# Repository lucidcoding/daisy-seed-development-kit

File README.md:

# Daisy Seed Development Kit

## Author

Paul Davies

## Description

A modular development kit for the Electrosmith Daisy Seed development board. Currently modules include the central breakout board, a MIDI adapter and an array of 16 potentiometers. The breakout board includes connections for a second potentiometer array, SPI, I2C, an encoder and an SD card.

## Environment Setup

Ensure you have LIBDAISY_DIR and DAISYSP_DIR environment variables set and pointing to the relevant libraries. If you are using Windows, ensure they use the forward slash. If you are on Linux, ensure the capitalisation is correct. You'll make your life a lot easier if you don't have spaces in the path:

```
LIBDAISY_DIR=/path/to/libdaisy
DAISYSP_DIR=/path/to/daisysp
```

## Getting up and running

In order to build the hardware, load each of the projects in to Kicad, generate Gerber files and upload to a PCB manufacturer such as https://jlcpcb.com/. I can go into more detail about this at a later point.

The to get started, load the MonoSeed09 project on to the Daisy Seed by pressing both buttons to put it into program mode, entering the relevant folder, then enetering the commands to upload the code onto the Seed:

```
cd Examples/MonoSeed09
make clean; make; make program-dfu;
```

Ensure the Daisy Seed is correctly seated in the breakout board. Then connect the potentiometer array to port 1 with a JST XH2.54 8 wire cable, and connect the MIDI adapter with a JST XH2.54 4 wire cable. Finally connect your MIDI sequencer to the MIDI in DIN connector and plug your headphones into the audio out jack socket.

## Disclaimer

Although I am a professional programmer, I am purely a hobbyist when it comes to hardware or embedded programming. There may well be some mistakes here and I accept no responsibility for damage to you Daisy Seed, external equipment or anything else. You use this code and harware at your own risk.

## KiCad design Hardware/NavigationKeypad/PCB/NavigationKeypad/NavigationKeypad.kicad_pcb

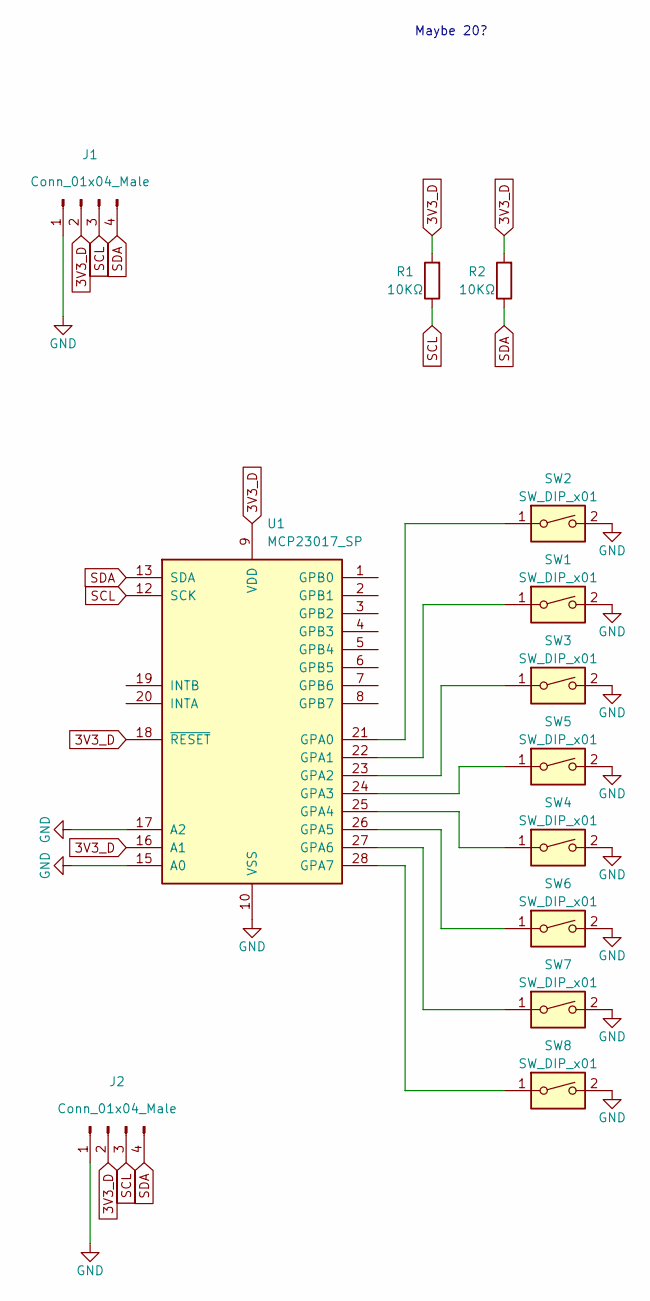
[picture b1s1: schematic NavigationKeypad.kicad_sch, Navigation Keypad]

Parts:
J1: Conn_01x04_Male; PinHeader_1x04_P2.54mm_Horizontal
J2: Conn_01x04_Male; PinSocket_1x04_P2.54mm_Horizontal
R1, R2: 10KΩ; R_Axial_DIN0207_L6.3mm_D2.5mm_P10.16mm_Horizontal
SW1, SW2, SW3, SW4, SW5, SW6, SW7, SW8: SW_DIP_x01; SW_PUSH_6mm
U1: MCP23017_SP; DIP-28_W7.62mm

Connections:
3V3_D: J1.2, J2.2, R1.2, R2.2, U1.9 (VDD), U1.16 (A1), U1.18 (~RESET)
GND: J1.1, J2.1, SW1.2, SW2.2, SW3.2, SW4.2, SW5.2, SW6.2, SW7.2, SW8.2, U1.10 (VSS), U1.15 (A0), U1.17 (A2)
unnamed: SW2.1, U1.21 (GPA0)
unnamed: SW1.1, U1.22 (GPA1)
unnamed: SW3.1, U1.23 (GPA2)
unnamed: SW5.1, U1.24 (GPA3)
unnamed: SW4.1, U1.25 (GPA4)
unnamed: SW6.1, U1.26 (GPA5)
unnamed: SW7.1, U1.27 (GPA6)
unnamed: SW8.1, U1.28 (GPA7)
SCL: J1.3, J2.3, R1.1, U1.12 (SCK)
SDA: J1.4, J2.4, R2.1, U1.13 (SDA)

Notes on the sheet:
Maybe 20?

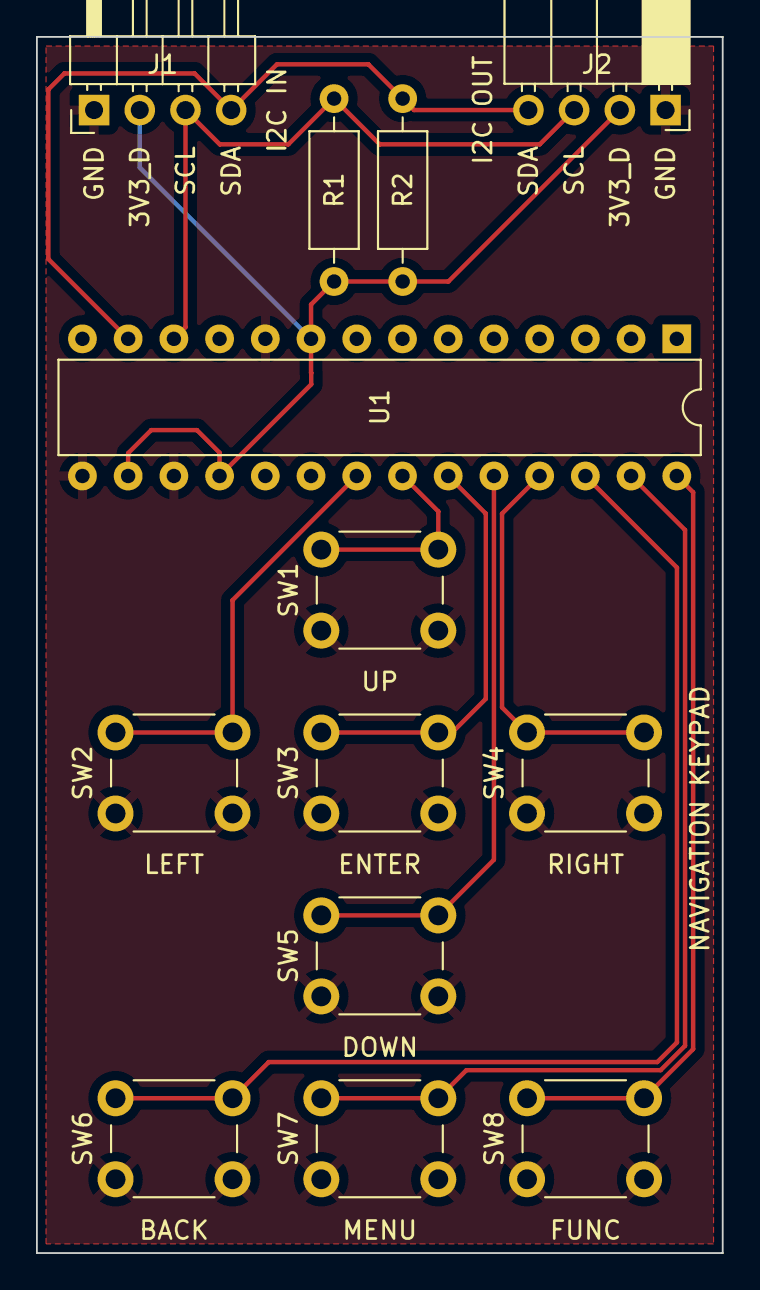
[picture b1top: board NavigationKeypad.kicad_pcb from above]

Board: 2 copper layers, 38.1 x 67.6 mm, 13 parts (0 on the bottom side), 12 nets.

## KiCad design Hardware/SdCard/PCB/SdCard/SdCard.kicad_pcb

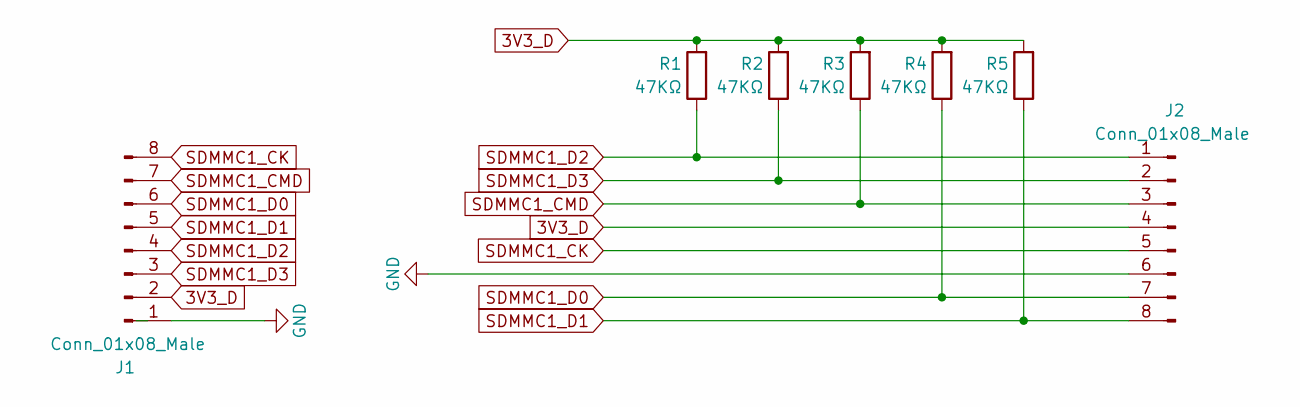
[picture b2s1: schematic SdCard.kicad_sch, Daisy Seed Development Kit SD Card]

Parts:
J1: Conn_01x08_Male; PinHeader_1x08_P2.54mm_Horizontal
J2: Conn_01x08_Male; PinHeader_1x08_P2.00mm_Vertical
R1, R2, R3, R4, R5: 47KΩ; R_Axial_DIN0207_L6.3mm_D2.5mm_P10.16mm_Horizontal

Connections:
3V3_D: J1.2, J2.4, R1.2, R2.2, R3.2, R4.2, R5.2
GND: J1.1, J2.6
SDMMC1_CK: J1.8, J2.5
SDMMC1_CMD: J1.7, J2.3, R3.1
SDMMC1_D0: J1.6, J2.7, R4.1
SDMMC1_D1: J1.5, J2.8, R5.1
SDMMC1_D2: J1.4, J2.1, R1.1
SDMMC1_D3: J1.3, J2.2, R2.1

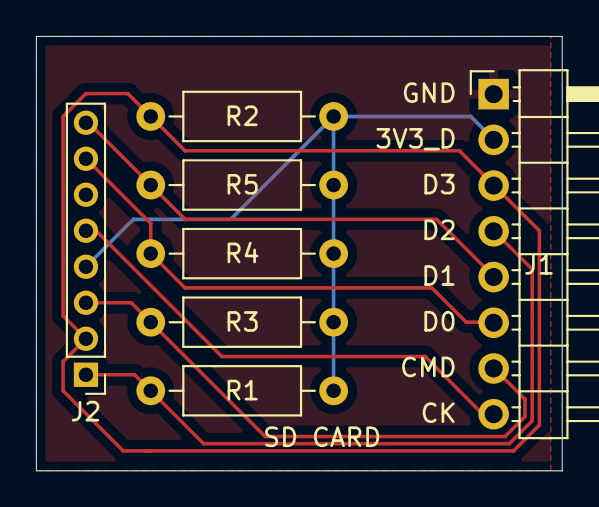
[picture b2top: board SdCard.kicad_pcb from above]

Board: 2 copper layers, 29.2 x 24.1 mm, 7 parts (0 on the bottom side), 8 nets.

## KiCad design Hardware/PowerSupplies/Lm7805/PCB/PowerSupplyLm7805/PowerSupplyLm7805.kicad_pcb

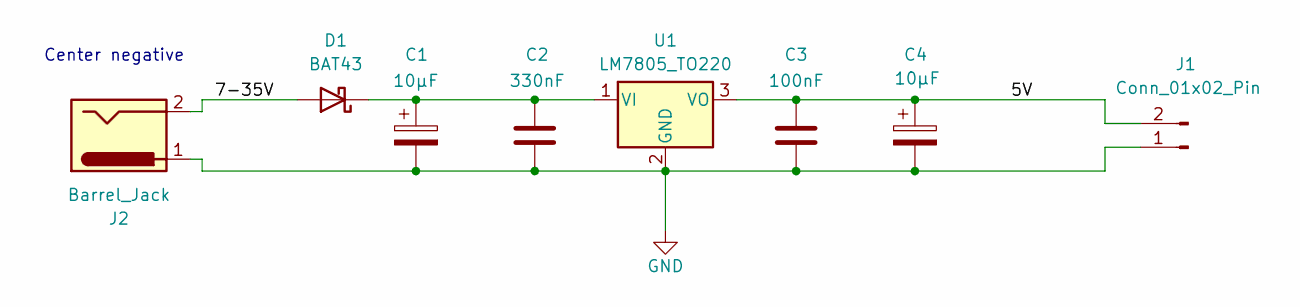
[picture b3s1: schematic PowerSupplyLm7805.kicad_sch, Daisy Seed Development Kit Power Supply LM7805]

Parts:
C1, C4: 10μF; C_Radial_D6.3mm_H7.0mm_P2.50mm
C2: 330nF; C_Disc_D5.0mm_W2.5mm_P5.00mm
C3: 100nF; C_Disc_D5.0mm_W2.5mm_P2.50mm
D1: BAT43; D_DO-35_SOD27_P7.62mm_Horizontal
J1: Conn_01x02_Pin; PinSocket_1x02_P2.54mm_Horizontal
J2: Barrel_Jack; BarrelJack_GCT_DCJ200-10-A_Horizontal
U1: LM7805_TO220; TO-220-3_Vertical

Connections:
/5V: C3.1, C4.1, J1.2, U1.3 (VO)
/7-35V: D1.2 (A), J2.2
GND: C1.2, C2.2, C3.2, C4.2, J1.1, J2.1, U1.2 (GND)
unnamed: C1.1, C2.1, D1.1 (K), U1.1 (VI)

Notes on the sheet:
Center negative

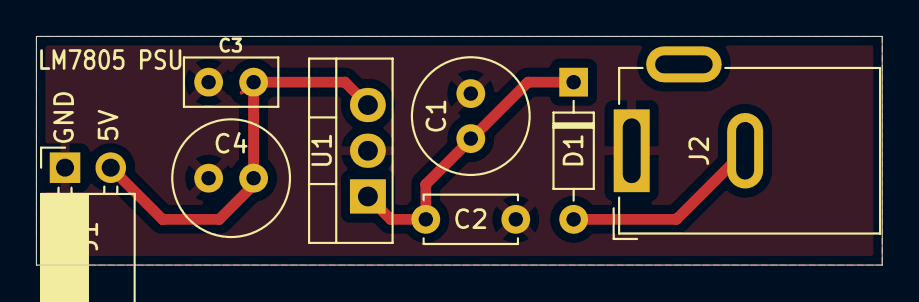
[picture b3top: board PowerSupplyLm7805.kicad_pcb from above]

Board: 2 copper layers, 47.0 x 12.7 mm, 8 parts (0 on the bottom side), 4 nets.

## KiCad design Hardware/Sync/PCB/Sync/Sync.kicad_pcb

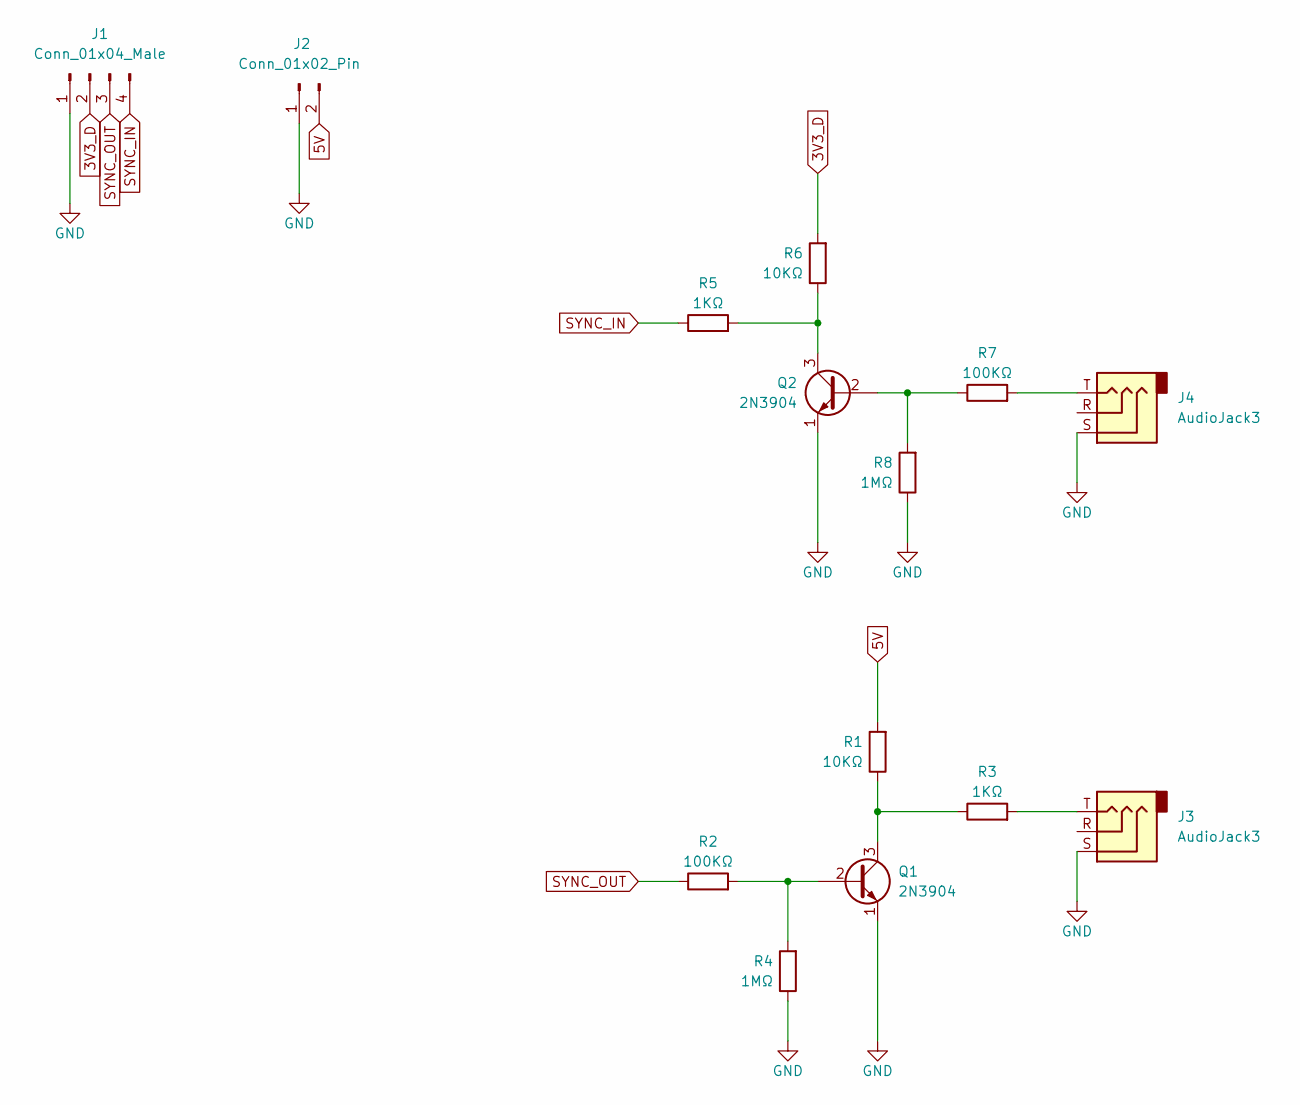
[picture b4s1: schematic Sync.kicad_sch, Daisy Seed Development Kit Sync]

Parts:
J1: Conn_01x04_Male; PinHeader_1x04_P2.54mm_Horizontal
J2: Conn_01x02_Pin; PinHeader_1x02_P2.54mm_Horizontal
J3, J4: AudioJack3; PJ-307
Q1, Q2: 2N3904; TO-92_Inline
R1, R6: 10KΩ; R_Axial_DIN0207_L6.3mm_D2.5mm_P10.16mm_Horizontal
R2, R7: 100KΩ; R_Axial_DIN0207_L6.3mm_D2.5mm_P10.16mm_Horizontal
R3, R5: 1KΩ; R_Axial_DIN0207_L6.3mm_D2.5mm_P10.16mm_Horizontal
R4, R8: 1MΩ; R_Axial_DIN0207_L6.3mm_D2.5mm_P10.16mm_Horizontal

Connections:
3V3_D: J1.2, R6.2
5V: J2.2, R1.2
GND: J1.1, J2.1, J3.S, J4.S, Q1.1 (E), Q2.1 (E), R4.1, R8.1
unnamed: J3.T, R3.2
unnamed: J4.T, R7.2
unnamed: Q1.2 (B), R2.2, R4.2
unnamed: Q1.3 (C), R1.1, R3.1
unnamed: Q2.2 (B), R7.1, R8.2
unnamed: Q2.3 (C), R5.2, R6.1
SYNC_IN: J1.4, R5.1
SYNC_OUT: J1.3, R2.1

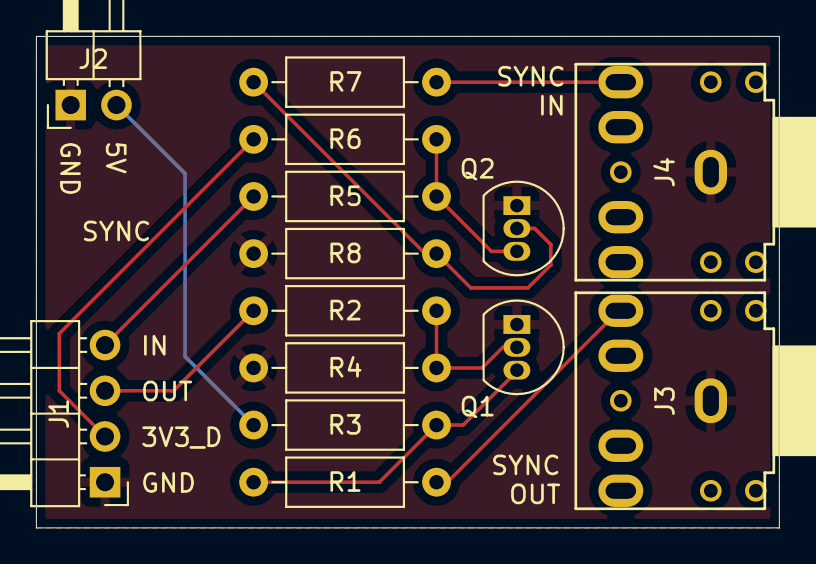
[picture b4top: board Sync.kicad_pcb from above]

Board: 2 copper layers, 41.3 x 27.3 mm, 14 parts (0 on the bottom side), 11 nets.

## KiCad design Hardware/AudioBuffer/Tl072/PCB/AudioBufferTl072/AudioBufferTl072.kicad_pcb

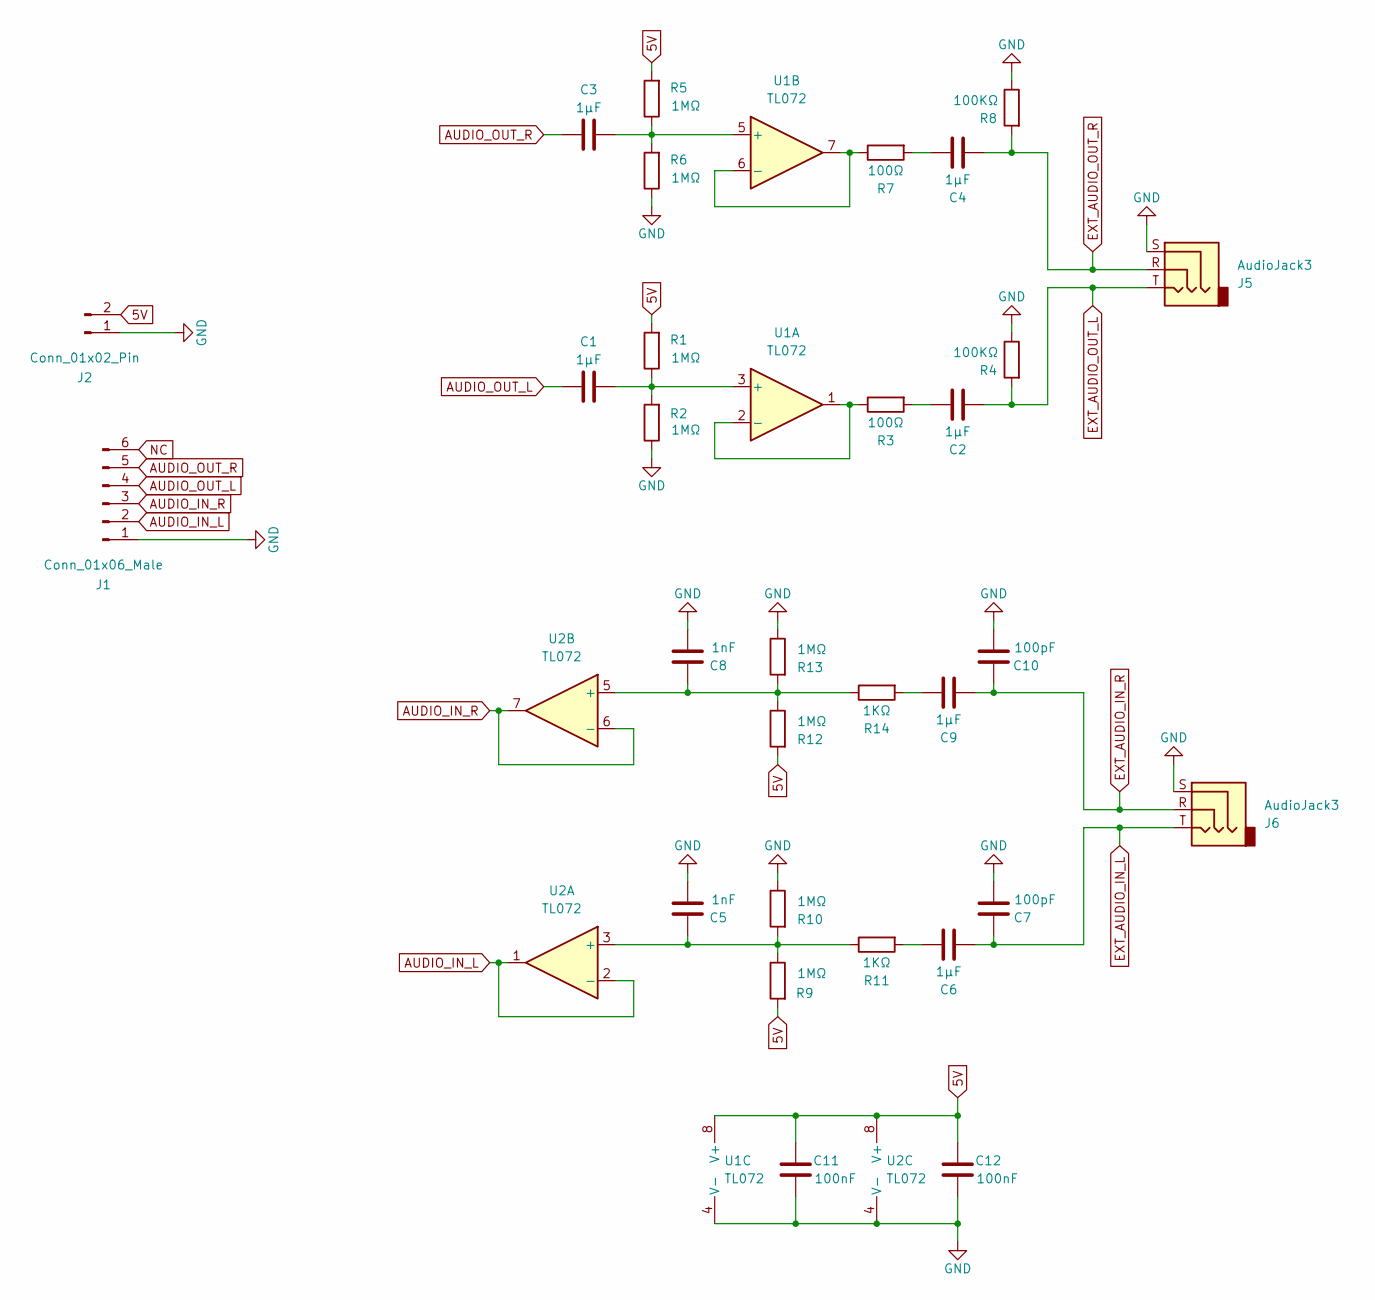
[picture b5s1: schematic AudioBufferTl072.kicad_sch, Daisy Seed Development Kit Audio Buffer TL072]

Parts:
C1, C2, C3, C4: 1μF; C_Disc_D5.0mm_W2.5mm_P2.50mm
C5, C8: 1nF; C_Disc_D5.0mm_W2.5mm_P2.50mm
C6, C9: 1μF; C_Disc_D5.0mm_W2.5mm_P5.00mm
C7, C10: 100pF; C_Disc_D5.0mm_W2.5mm_P2.50mm
C11, C12: 100nF; C_Disc_D5.0mm_W2.5mm_P2.50mm
J1: Conn_01x06_Male; PinHeader_1x06_P2.54mm_Horizontal
J2: Conn_01x02_Pin; PinHeader_1x02_P2.54mm_Horizontal
J5, J6: AudioJack3; PJ-307
R1, R2, R5, R6, R9, R10, R12, R13: 1MΩ; R_Axial_DIN0207_L6.3mm_D2.5mm_P10.16mm_Horizontal
R3, R7: 100Ω; R_Axial_DIN0207_L6.3mm_D2.5mm_P10.16mm_Horizontal
R4, R8: 100KΩ; R_Axial_DIN0207_L6.3mm_D2.5mm_P10.16mm_Horizontal
R11, R14: 1KΩ; R_Axial_DIN0207_L6.3mm_D2.5mm_P10.16mm_Horizontal
U1, U2: TL072; DIP-8_W7.62mm

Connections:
5V: C11.1, C12.1, J2.2, R1.2, R5.2, R9.2, R12.2, U1.8 (V+), U2.8 (V+)
AUDIO_IN_L: J1.2, U2.1, U2.2 (-)
AUDIO_IN_R: J1.3, U2.6 (-), U2.7
AUDIO_OUT_L: C1.1, J1.4
AUDIO_OUT_R: C3.1, J1.5
EXT_AUDIO_IN_L: C6.2, C7.1, J6.T
EXT_AUDIO_IN_R: C9.2, C10.1, J6.R
EXT_AUDIO_OUT_L: C2.2, J5.T, R4.2
EXT_AUDIO_OUT_R: C4.2, J5.R, R8.2
GND: C5.2, C7.2, C8.2, C10.2, C11.2, C12.2, J1.1, J2.1, J5.S, J6.S, R2.1, R4.1, R6.1, R8.1, R10.1, R13.1, U1.4 (V-), U2.4 (V-)
NC: J1.6
unnamed: C2.1, R3.2
unnamed: C4.1, R7.2
unnamed: C6.1, R11.2
unnamed: C9.1, R14.2
unnamed: C1.2, R1.1, R2.2, U1.3 (+)
unnamed: R3.1, U1.1, U1.2 (-)
unnamed: C3.2, R5.1, R6.2, U1.5 (+)
unnamed: R7.1, U1.6 (-), U1.7
unnamed: C5.1, R9.1, R10.2, R11.1, U2.3 (+)
unnamed: C8.1, R12.1, R13.2, R14.1, U2.5 (+)

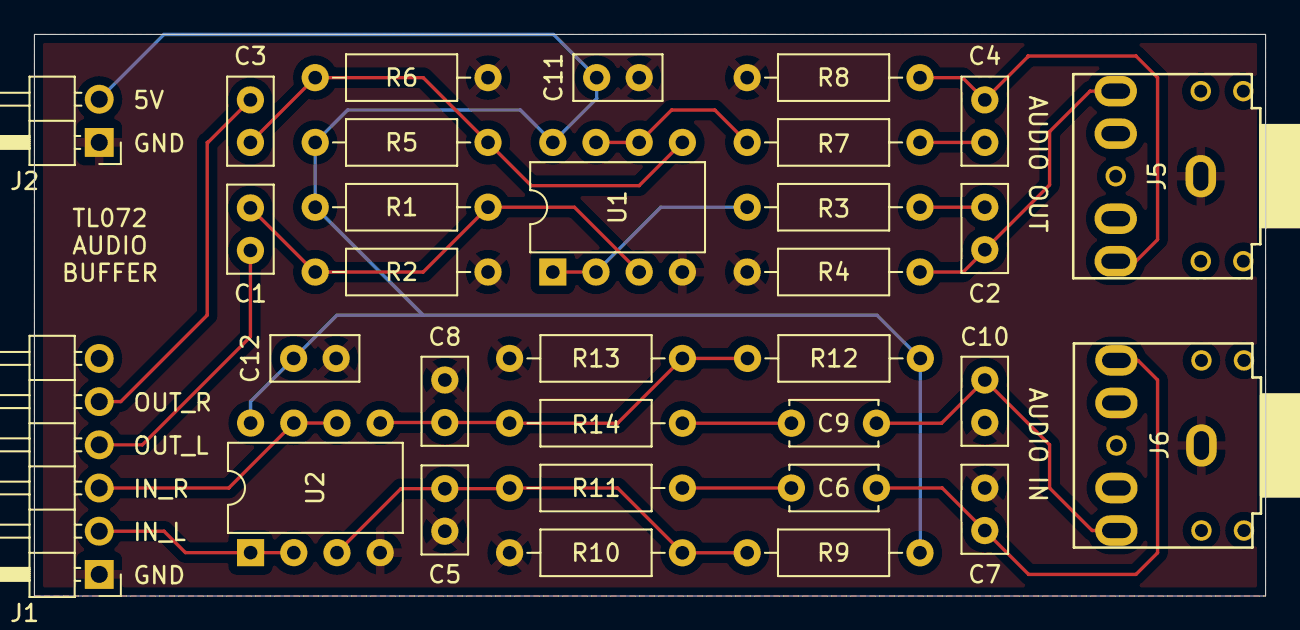
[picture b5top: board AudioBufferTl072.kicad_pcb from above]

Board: 2 copper layers, 72.4 x 33.0 mm, 32 parts (0 on the bottom side), 20 nets.

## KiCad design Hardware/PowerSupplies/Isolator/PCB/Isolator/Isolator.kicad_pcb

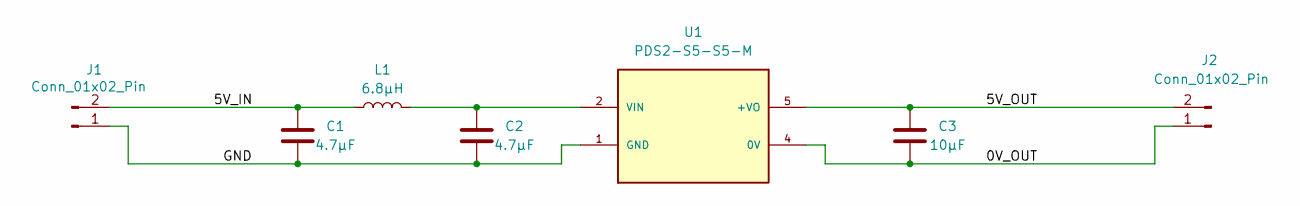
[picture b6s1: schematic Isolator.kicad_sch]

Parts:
C1, C2: 4.7μF; C_Disc_D5.0mm_W2.5mm_P5.00mm
C3: 10μF; C_Disc_D5.0mm_W2.5mm_P5.00mm
J1: Conn_01x02_Pin; PinHeader_1x02_P2.54mm_Horizontal
J2: Conn_01x02_Pin; PinSocket_1x02_P2.54mm_Horizontal
L1: 6.8μH; L_Radial_D7.0mm_P3.00mm
U1: PDS2-S5-S5-M; CONV_PDS2-S5-S5-M

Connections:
/0V_OUT: C3.2, J2.1, U1.4 (0V)
/5V_IN: C1.1, J1.2, L1.1
/5V_OUT: C3.1, J2.2, U1.5 (+VO)
/GND: C1.2, C2.2, J1.1, U1.1 (GND)
unnamed: C2.1, L1.2, U1.2 (VIN)

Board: 2 copper layers, 7 parts (0 on the bottom side), 5 nets, no tracks yet.

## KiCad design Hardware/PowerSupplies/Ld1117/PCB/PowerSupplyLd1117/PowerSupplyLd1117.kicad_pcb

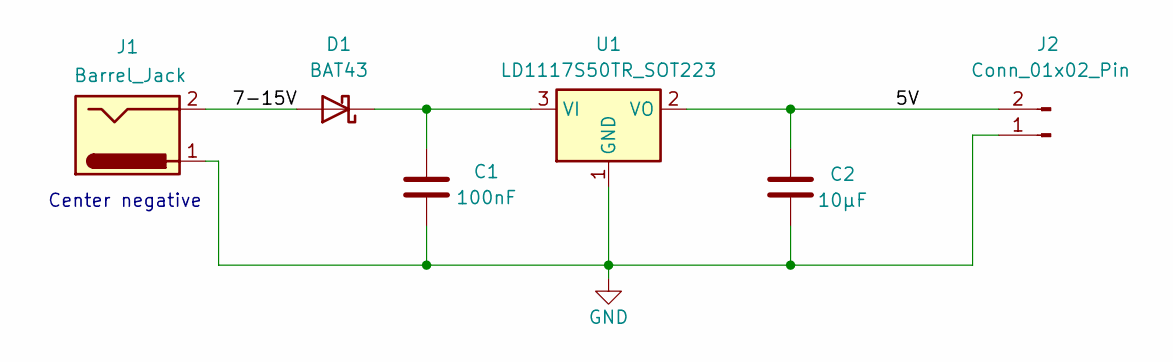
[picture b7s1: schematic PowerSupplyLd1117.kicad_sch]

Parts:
C1: 100nF; C_Disc_D5.0mm_W2.5mm_P2.50mm
C2: 10μF; C_Disc_D5.0mm_W2.5mm_P5.00mm
D1: BAT43; D_DO-35_SOD27_P7.62mm_Horizontal
J1: Barrel_Jack; BarrelJack_GCT_DCJ200-10-A_Horizontal
J2: Conn_01x02_Pin; PinSocket_1x02_P2.54mm_Horizontal
U1: LD1117S50TR_SOT223; SOT-223-3_TabPin2

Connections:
/5V: C2.1, J2.2, U1.2 (VO)
/7-15V: D1.2 (A), J1.2
GND: C1.2, C2.2, J1.1, J2.1, U1.1 (GND)
unnamed: C1.1, D1.1 (K), U1.3 (VI)

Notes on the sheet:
Center negative

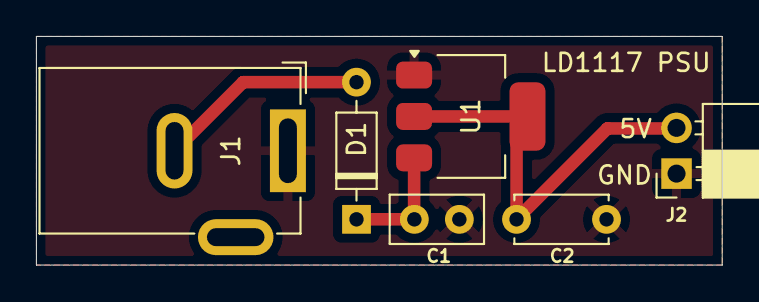
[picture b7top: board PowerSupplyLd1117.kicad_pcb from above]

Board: 2 copper layers, 38.1 x 12.7 mm, 6 parts (0 on the bottom side), 4 nets.

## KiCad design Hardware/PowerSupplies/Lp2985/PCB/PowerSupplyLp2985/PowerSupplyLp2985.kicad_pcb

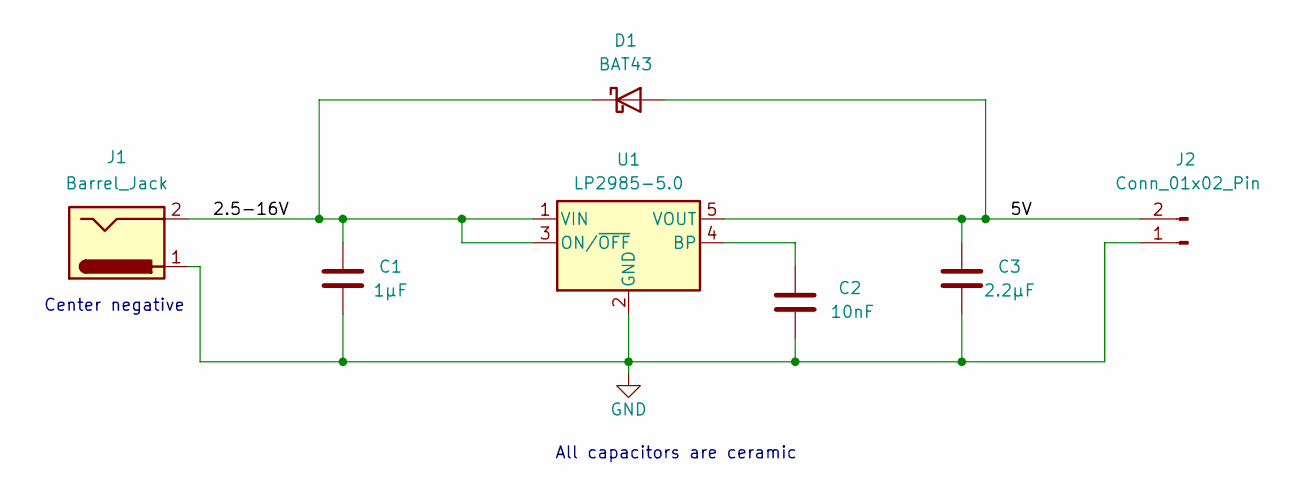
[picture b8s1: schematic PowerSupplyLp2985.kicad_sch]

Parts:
C1: 1μF; C_Disc_D5.0mm_W2.5mm_P5.00mm
C2: 10nF; C_Disc_D5.0mm_W2.5mm_P2.50mm
C3: 2.2μF; C_Disc_D5.0mm_W2.5mm_P5.00mm
D1: BAT43; D_DO-35_SOD27_P7.62mm_Horizontal
J1: Barrel_Jack; BarrelJack_GCT_DCJ200-10-A_Horizontal
J2: Conn_01x02_Pin; PinSocket_1x02_P2.54mm_Horizontal
U1: LP2985-5.0; SOT-23-5

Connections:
/2.5-16V: C1.1, D1.1 (K), J1.2, U1.1 (VIN), U1.3 (ON/~OFF)
/5V: C3.1, D1.2 (A), J2.2, U1.5 (VOUT)
GND: C1.2, C2.1, C3.2, J1.1, J2.1, U1.2 (GND)
unnamed: C2.2, U1.4 (BP)

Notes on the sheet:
All capacitors are ceramic
Center negative

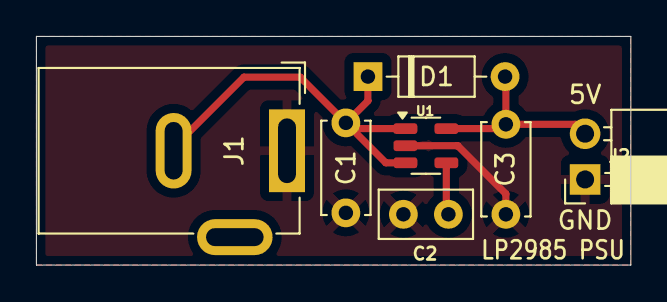
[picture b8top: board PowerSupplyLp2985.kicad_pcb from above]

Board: 2 copper layers, 33.0 x 12.7 mm, 7 parts (0 on the bottom side), 4 nets.

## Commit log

2023-11-02 Removing .vscode from github
2023-11-02 Removed Makefile from .gitignore
2023-11-03 Implementing minimum pulse width
2023-11-05 Updated schematic annotations and README.md
2023-11-06 Tidy up of MonoSeed09
2023-11-06 Added potentiometer layout diagram
2023-11-06 Youtube link added
2023-11-08 Added unchecked schematic for external codec
2023-11-09 Added codec diagram
2023-11-12 External codec Kicad files added
2023-11-13 ExternalCodec drivers added
2023-11-24 Updated external codec drivers and tests
2023-11-24 Updated diagram
2023-12-20 Initial test for StepSequencer
2023-12-21 Leds and Keys in own file and running together
2023-12-22 Tuned performance of Leds and Keys
2023-12-27 Tuning to keys and leds
2023-12-28 Added programming
2023-12-28 Renaming Process
2023-12-28 Moved dependencies to interfaces
2023-12-28 Leds moved to interface
2023-12-28 Passing in time
2023-12-30 Put back pot array schematic
2023-12-31 Moved step sequencer to branch
2023-12-31 Moved sequencer to branch and added Catch2
2023-12-31 Refactored so sequencer does not have dependencies
2023-12-31 Getting tests up and running
2024-01-01 Simplified reverse lookup of array
2024-01-01 Removed some magic numbers
2024-01-01 Removed more magic numbers
2024-01-01 More cleaning
2024-01-02 Producing sounds
2024-01-02 Gates and slides implemented
2024-01-06 Slides and oct up/down in place
2024-01-06 Accents added
2024-01-11 Added gates
2024-01-11 Started putting tests in place
2024-01-11 Test fixes
2024-01-12 All tests passing
2024-01-12 Refactoring key presses
2024-01-14 Tests for programming sequencer
2024-01-14 Fixed tests for note entry
2024-01-15 LED testing in place
2024-01-15 Fix to gate programming
2024-01-15 Hardcoded step count for now
2024-01-15 Tidy up
2024-01-15 Added slides and accents to standalone test
2024-01-15 Refactored into BassSeed303
2024-01-15 Renaming of target
2024-01-17 Removed slides from frequency for now
2024-01-17 Renamed SequencerBrain to Controller
2024-01-18 Recording multiple key press and tart of new hardware
2024-01-22 Hardware update
2024-01-22 Finished interface and renaming
2024-01-23 Refactor of BassSeed
2024-01-23 Moved keys and leds into interface class
2024-01-24 Modified makefiles
2024-01-24 General refactoring
2024-01-24 More of the synth engine in place
2024-01-24 Attempt at getting tempo parameter in
2024-01-29 Initial alt experiment
2024-01-29 Changing to using ticks
2024-01-30 Simplified Leds
2024-01-30 Added constant for scan time
2024-01-30 Interface tidied up
2024-01-30 Tests passing again
2024-01-30 Fixed issue where starting on second step
2024-01-30 Refactoring
2024-01-30 Debouncing improved
2024-01-30 Debounce tuning
2024-02-02 General project structure refactor
2024-02-02 Moved out step sequencer for now
2024-02-02 Readded step sequencer elements
2024-02-02 Most elements working
2024-02-02 Passing through parameters to osc
2024-02-05 Main part of framework and manual test set up
2024-02-05 Abstracted out UiParameterProvider
2024-02-05 UiParameter tests in place
2024-02-05 Changed init values
2024-02-05 Abstracted out View from ListPage
2024-02-05 Unit tests for display in place
2024-02-05 Readme added
2024-02-05 Removed redundat file
2024-02-07 Configured drivers to new hardware
2024-02-08 Tweaks to interface
2024-02-08 Change back to interface config
2024-02-09 Updated controller to work with new hardware
2024-02-10 Screen now working
2024-02-11 Hysteresis on analog control display
2024-02-11 Modifying values on change
2024-02-12 Ability to pass in different view
2024-02-13 Added third party in
2024-02-13 ListPage ported to TFT and TabPage started
2024-02-13 Separated out tree and tabs
2024-02-14 Tabbed pages with pot values
2024-02-15 Modified passing of pot values
2024-02-15 Tabs tests reorganised
2024-02-18 reating values between page switches
2024-02-18 Setting if synced on first reading
2024-02-18 Hysteresis band added to display value
2024-02-18 Tidy up and test on hysteresis decrement
2024-02-18 Added in catch mode
2024-02-19 Refactoring into own class
2024-02-19 Added new scalers
2024-02-19 Refactored scaling
2024-02-19 Ability to pass options added
2024-02-20 Separating out continuous and stepped
2024-02-20 Clean up of code
2024-02-20 Tidying up and refactoring
2024-02-21 All 16 inputs on MultiValueTests
2024-02-21 Refactoring tree to match tab
2024-02-22 Refactored tree version
2024-02-23 Start of applying to synth
2024-02-23 Started merging tree and tabs
2024-02-23 Using ViewAdapters
2024-02-23 Clean up
2024-02-24 Added view adapter for ILI9394
2024-02-25 Renamed PageItem ListPageItem
2024-02-26 Tabs brought into generic version
2024-02-26 Added in WriteStringAligned
2024-02-26 Removing reference to <string>
2024-02-26 Fixed memory issues and hooked up to values
2024-02-27 Fixed square wave selector
2024-02-28 Collating unit tests
2024-02-28 Tidy up of tests
2024-02-29 All unit tests included
2024-02-29 Ensure all manual tests are working OK
2024-02-29 Tidying up of namespaces
2024-03-01 Rearranged folder structure
2024-03-01 Removed redundant files
2024-03-02 Adding of hardware
2024-03-02 Navigation keypad added
2024-03-05 Renamed codecs, added buffer and PCM3060 codec
2024-03-06 Added 7805 PSU
2024-03-06 Sync added
2024-03-08 Updated to PCM3060
2024-03-10 power supplies added
2024-03-11 Added consistency
2024-03-11 Updates to audio buffer
2024-03-11 SD Card added
2024-03-13 Isolator added
2024-03-13 Removing edge and mount holes
2024-03-13 Finalised PCBs
2024-03-13 Edges removed
2024-03-13 Removed 7805
2024-03-13 Added PSU
2024-03-13 Created gerbers
2024-03-13 Experimenting with parameters
2024-03-14 Sound engine tweaking
2024-03-14 Tests fixed
2024-03-14 Sound engine tweaks
2024-03-14 Moved scaling and added README
2024-03-15 Modified way key presses are recorded
2024-03-15 SeqSyncSource select functionality added
2024-03-16 Added clear functionality
2024-03-21 Added save UI mechanism
2024-03-21 Added save mechanism
2024-03-21 Saving to hardware
2024-03-23 Added saving of pattern
2024-03-23 Chaged seq sync to constants
2024-03-23 refactored out leds to stopState
2024-03-23 Added play and stepRec states
2024-03-24 Moved out setSeqSyncState leds
2024-03-24 Refactored out blink
2024-03-24 Deferring to blinState when saving
2024-03-24 Replace saving and cl.earing mode with blink
2024-03-24 Added save state
2024-03-24 Using state interface
2024-03-24 Moving out key press reaction
2024-03-25 Modified way gate works
2024-03-25 Added reset
2024-03-25 Moved out all clock events
2024-03-25 Moved play out to states
2024-03-25 StepRecState butoon presses moved out
2024-03-25 Moving save into state
2024-03-25 All key presses in state
2024-03-25 Moved key releases into state
2024-03-25 More refactoring
2024-03-25 Load mode working
2024-03-25 Fixed load tests
2024-03-25 Can change pattern while playing
2024-03-29 Starting play during load from start of bar
2024-03-31 Sandpitting sync
2024-03-31 Sync driver added
2024-04-01 Sync added and tests in place
2024-04-01 Refactored click and key press into same event
2024-04-03 Nice debug mechanism added
2024-04-05 Passing pulse through
2024-04-06 Working in sync, but can't cue at the right time
2024-04-06 All seems to sync and cue correctly
2024-04-06 Specific methods for changing state
2024-04-07 Moving some functionality into utility class
2024-04-16 shelving for now
2024-04-16 Updated portamento
2024-08-06 Added settings page
2024-08-07 menu screen added
2024-08-12 Parameters in place
2024-08-16 Added midi and fixed unit tests
